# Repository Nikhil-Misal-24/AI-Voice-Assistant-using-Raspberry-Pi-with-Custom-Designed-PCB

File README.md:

This project focuses on the design and development of an intelligent AI-based voice assistant system implemented using 
the Raspberry Pi platform along with a custom-designed Printed Circuit Board (PCB).The system is developed to provide a compact, 
efficient, and real-time embedded solution for voice interaction, smart automation, and human-machine communication.

The custom PCB plays a crucial role in integrating essential hardware components such as microphone input circuitry for
voice command acquisition, audio output interface for speaker or amplifier connectivity, stable power regulation modules,
and peripheral interfacing required for reliable Raspberry Pi operation. This hardware-level optimization enhances system stability,
reduces wiring complexity, and makes the device suitable for real-world deployment.

(i) On the software side, the AI assistant is capable of recognizing voice commands, processing user inputs, executing predefined intelligent actions,
and interacting with connected IoT devices. The system can be extended to perform tasks such as information retrieval, device control, automation 
scheduling, and smart environment monitoring. The project demonstrates a practical combination of embedded system design, artificial intelligence 
concepts, and IoT integration.

(ii) Overall, this project serves as a strong implementation example for students, developers, and researchers interested in embedded AI, robotics,
smart home systems, and edge computing applications. It highlights the importance of hardware-software co-design in building scalable and efficient
intelligent assistant solutions.

AI-Based Voice Assistant (Raspberry Pi + Custom PCB) - Block Diagram

1) Input Section (Voice Acquisition):
   Microphone Module: User ki voice commands ko capture karta hai.
   I2S/USB Interface: Analog voice signal ko digital data mein convert karke Raspberry Pi tak pahunchata hai.
   
3) Processing Section (The Brain - Raspberry Pi):
   Raspberry Pi: Central processing unit jo sabhi operations ko coordinate karta hai.
   Software Stack: Ismein Speech-to-Text (STT), Intent Analysis (NLP), aur Text-to-Speech (TTS) engine shaamil hain.
   
4) Hardware Interface (Custom PCB):
   Voltage Regulation: Raspberry Pi aur peripherals ke liye stable power supply assure karta hai.
   Audio Amplifier Circuit: Audio signal ko amplify karta hai taaki speaker se clear sound aaye.
   Peripheral Connectivity: GPIO pins ke through sensors ya other devices ko connect karta hai.
   
5) Output Section (Feedback & Action):
   Speaker: Voice response deta hai.
   IoT Devices/Relays: Smart automation commands ko execute karta hai (jaise lights off karna).
   Status LEDs: System ka current status indicate karta hai (Listening, Processing, etc.)

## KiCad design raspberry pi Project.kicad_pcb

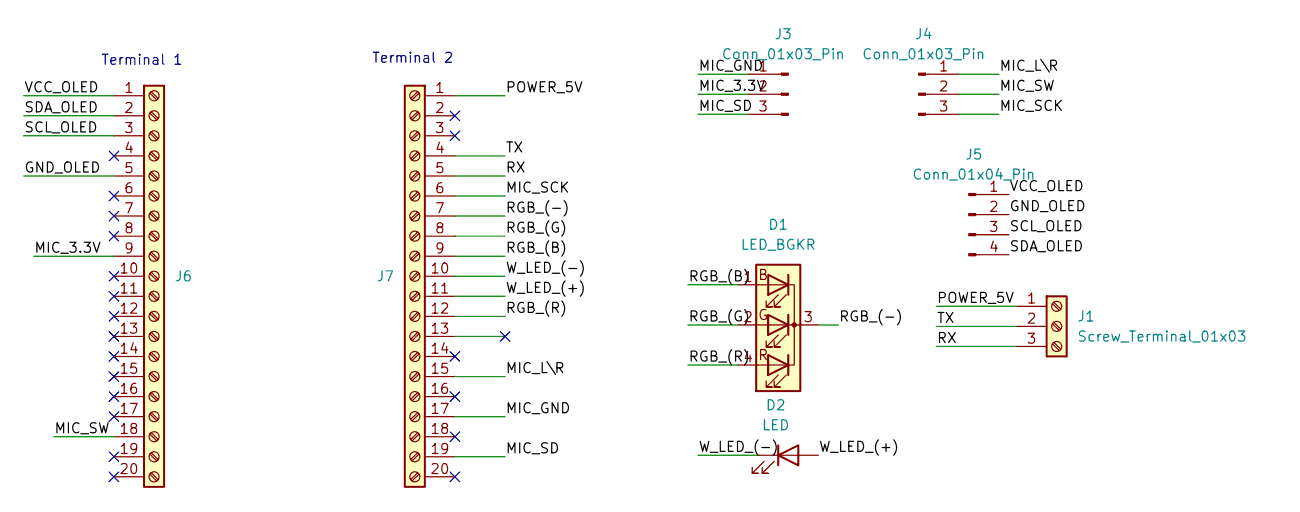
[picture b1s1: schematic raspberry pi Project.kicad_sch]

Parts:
D1: LED_BGKR; LED_D5.0mm-4_RGB
D2: LED; LED_D5.0mm
J1: Screw_Terminal_01x03; PinSocket_1x03_P2.54mm_Vertical
J3, J4: Conn_01x03_Pin; PinSocket_1x03_P2.54mm_Vertical
J5: Conn_01x04_Pin; PinSocket_1x04_P2.54mm_Vertical
J6, J7: Screw_Terminal_01x20; PinHeader_1x20_P2.54mm_Vertical

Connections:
/GND_OLED: J5.2, J6.5
/MIC_3.3V: J3.2, J6.9
/MIC_GND: J3.1, J7.17
/MIC_L\R: J4.1, J7.15
/MIC_SCK: J4.3, J7.6
/MIC_SD: J3.3, J7.19
/MIC_SW: J4.2, J6.18
/POWER_5V: J1.1, J7.1
/RGB_(-): D1.3 (K), J7.7
/RGB_(B): D1.1 (BA), J7.9
/RGB_(G): D1.2 (GA), J7.8
/RGB_(R): D1.4 (RA), J7.12
/RX: J1.3, J7.5
/SCL_OLED: J5.3, J6.3
/SDA_OLED: J5.4, J6.2
/TX: J1.2, J7.4
/VCC_OLED: J5.1, J6.1
/W_LED_(+): D2.2 (A), J7.11
/W_LED_(-): D2.1 (K), J7.10

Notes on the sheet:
Terminal 2
Terminal 1

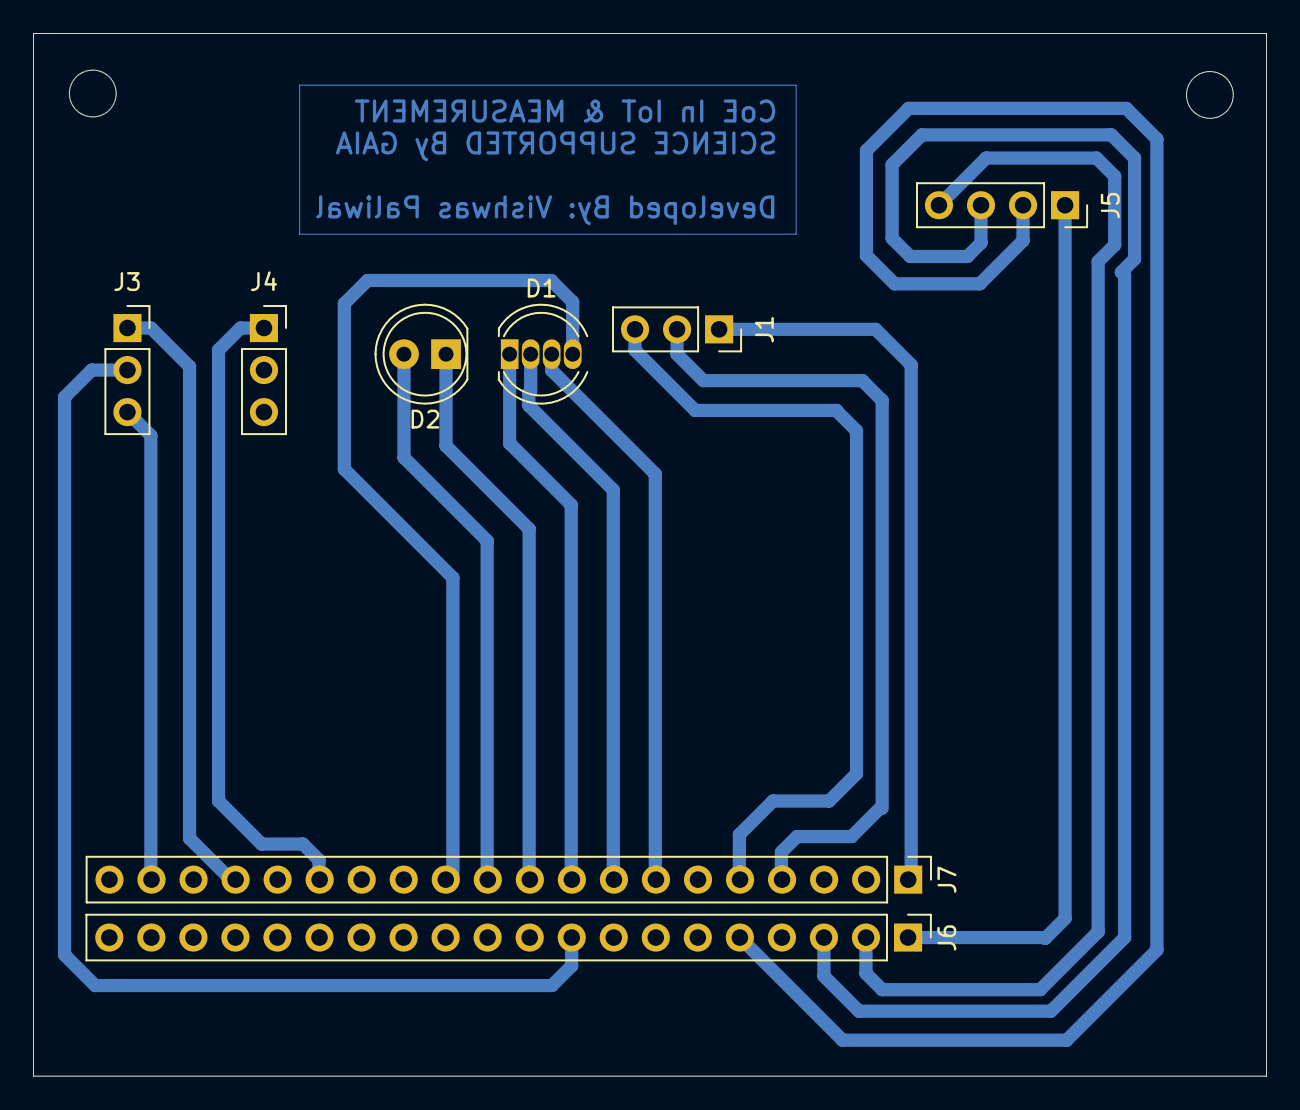
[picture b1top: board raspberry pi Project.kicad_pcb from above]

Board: 2 copper layers, 74.5 x 63.0 mm, 8 parts (0 on the bottom side), 19 nets.

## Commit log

2026-03-15 AI Assistsnt
2026-03-15 Add project overview and block diagram to README
    Added detailed project description and block diagram for the AI-based voice assistant system using Raspberry Pi and custom PCB.
2026-04-15 Fix formatting of status LEDs description in README
2026-04-15 Fix section numbering in README.md
2026-04-15 Fix formatting and enhance project description in README
    Corrected formatting issues in the README and improved clarity of project description.
2026-04-15 Fix formatting and improve readability in README
    Corrected formatting issues and added spaces after bullet points for better readability.
